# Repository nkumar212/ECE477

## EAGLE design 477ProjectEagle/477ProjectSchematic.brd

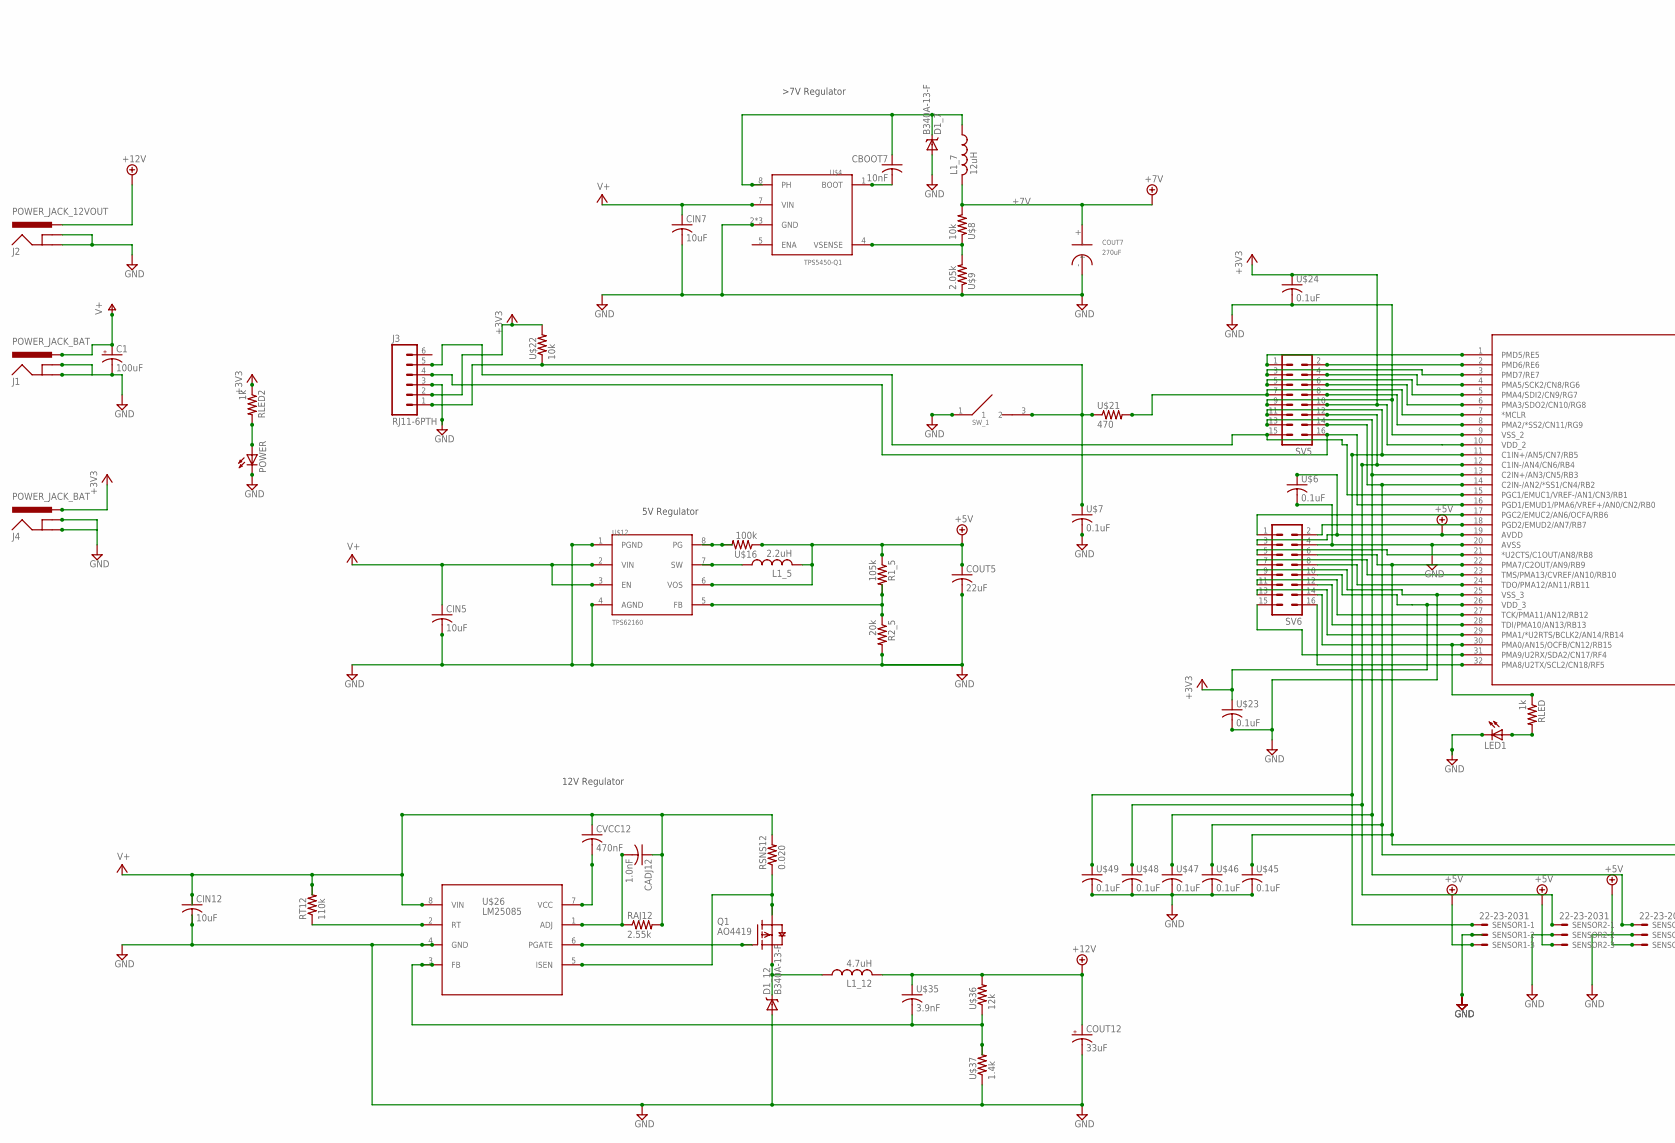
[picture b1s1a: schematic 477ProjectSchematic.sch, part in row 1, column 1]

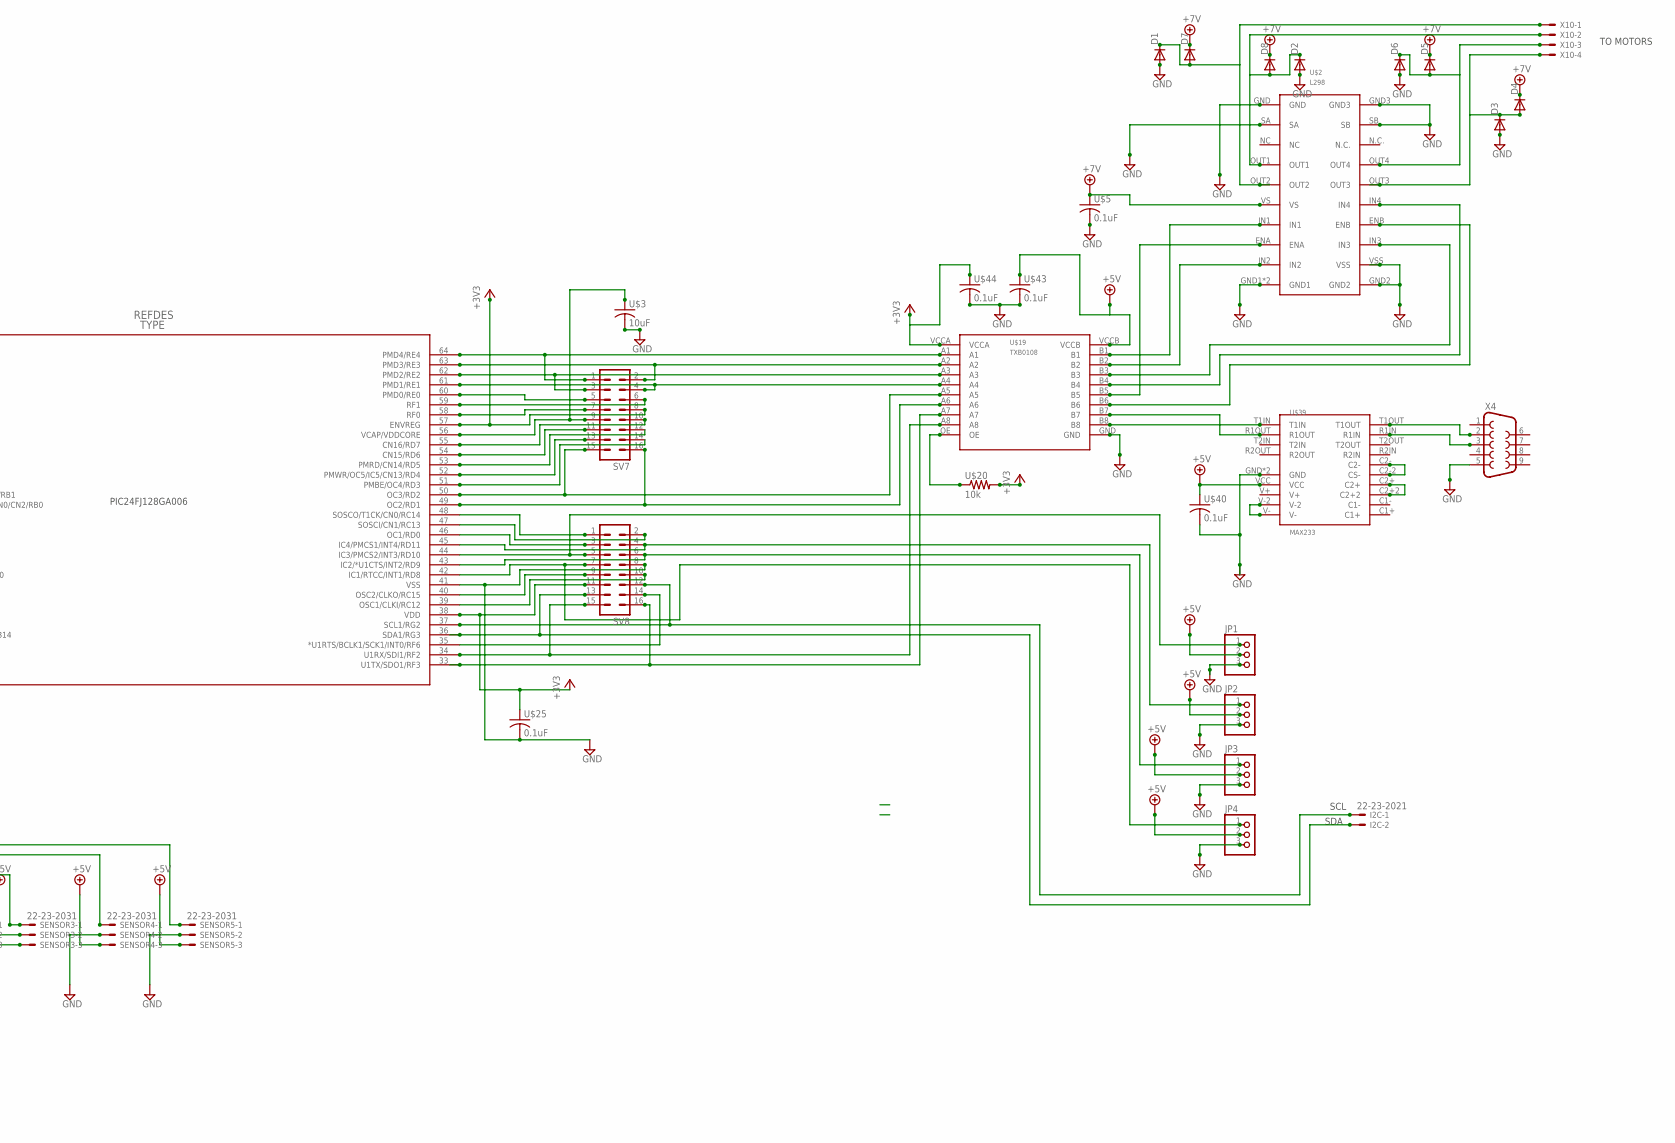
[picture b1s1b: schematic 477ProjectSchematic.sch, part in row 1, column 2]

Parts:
C1: 100uF; E3,5-8
CADJ12: 1.0nF; C1206
CBOOT7: 10nF; C1206
CIN5: 10uF; C1206
CIN7, CIN12: 10uF; C1210
COUT5: 22uF; C1206
COUT7: 270uF; CAPSMT_62_J80
COUT12: 33uF; D/7343-31W
CVCC12: 470nF; C1206
D1, D2, D3, D4, D5, D6, D7, D8: DIODE-DO-214AC; DO-214AC
D1_7, D1_12: B340A-13-F; SMA-DIODE
I2C: 22-23-2021
J1, J4: POWER_JACK_BAT; POWER_JACK_PTH
J2: POWER_JACK_12VOUT; POWER_JACK_PTH
J3: RJ11-6PTH; RJ11-6
JP1, JP2, JP3, JP4: PINHD-1X3; 1X03
L1_5: 2.2uH; SDR0403
L1_7: 12uH; SRR1210
L1_12: 4.7uH; SLF10165
LED1: LEDSMT1206; 1206
POWER: LEDSMT1206; 1206
Q1: AO4419; SOIC8
R1_5: 105k; R1206
R2_5: 20k; R1206
RAJ12: 2.55k; R1206
RLED, RLED2: 1k; R1206
RSNS12: 0.020; R1206
RT12: 110k; R1206
SENSOR1, SENSOR2, SENSOR3, SENSOR4, SENSOR5: 22-23-2031
SV5, SV6, SV7, SV8: MA08-2
SW_1: RESET_BUTTON; TACTILE-PTH-12MM
U$1: PIC24FJ128GA006-; TQFP64_10X10MC
U$2: L298
U$3: 10uF; C1206
U$4: TPS5450-Q1; PSOP-8
U$5, U$6, U$7, U$23, U$24, U$25, U$40, U$43, U$44, U$45, U$46, U$47, U$48, U$49: 0.1uF; C1206
U$8, U$20, U$22: 10k; R1206
U$9: 2.05k; R1206
U$12: TPS62160; MSOP-8
U$16: 100k; R1206
U$19: TXB0108
U$21: 470; R1206
U$26: LM25085; MSOP-8
U$35: 3.9nF; C1206
U$36: 12k; R1206
U$37: 1.4k; R1206
U$39: MAX233; SOIC-20
X4: DB9FEMALE; DB9
X10: 22-23-2041

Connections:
+3V3: J3.2, J4.PWR, RLED2.1, SV5.10, SV6.10, SV7.8, SV8.11, U$1.10 (VDD_2), U$1.26 (VDD_3), U$1.38 (VDD), U$1.57 (ENVREG), U$19.VCCA, U$20.2, U$22.2, U$23.1, U$24.1, U$25.1, U$44.1
+5V: COUT5.1, JP1.2, JP2.2, JP3.2, JP4.2, L1_5.B (2), R1_5.1, SENSOR1.3, SENSOR2.3, SENSOR3.3, SENSOR4.3, SENSOR5.3, SV6.3, U$1.19 (AVDD), U$6.1, U$12.6 (VOS), U$16.1, U$19.VCCB, U$39.VCC, U$40.1, U$43.1
+7V: COUT7.+, D4.C, D5.C, D7.C, D8.C, L1_7.B (2), U$2.VS, U$5.1, U$8.2
+12V: COUT12.+, J2.PWR, L1_12.2, U$35.1, U$36.2
GND: C1.-, CIN5.2, CIN7.2, CIN12.2, COUT5.2, COUT7.-, COUT12.-, D1.A, D1_7.-, D1_12.-, D2.A, D3.A, D6.A, J1.GND, J1.GNDBREAK, J2.GND, J2.GNDBREAK, J3.3, J4.GND, J4.GNDBREAK, JP1.3, JP2.3, JP3.3, JP4.3, LED1.C, POWER.C, R2_5.2, SENSOR1.2, SENSOR2.2, SENSOR3.2, SENSOR4.2, SENSOR5.2, SV5.9, SV6.4, SV6.9, SV8.8, SW_1.1, U$1.9 (VSS_2), U$1.20 (AVSS), U$1.25 (VSS_3), U$1.41 (VSS), U$2.GND, U$2.GND1, U$2.GND2, U$2.GND3, U$2.GNDPAD (GND1), U$2.SA, U$2.SB, U$2.VSS, U$3.2, U$4.2 (GND), U$4.6 (GND), U$4.PAD (GND), U$5.2, U$6.2, U$7.2, U$9.1, U$12.1 (PGND), U$12.4 (AGND), U$19.GND, U$23.2, U$24.2, U$25.2, U$26.4 (GND), U$37.1, U$39.GND, U$39.GND2 (GND), U$40.2, U$43.2, U$44.2, U$45.2, U$46.2, U$47.2, U$48.2, U$49.2, X4.5
unnamed: SENSOR1.1, SV5.11, U$1.11 (C1IN+/AN5/CN7/RB5), U$49.1
unnamed: SENSOR2.1, SV5.12, U$1.12 (C1IN-/AN4/CN6/RB4), U$48.1
unnamed: SENSOR3.1, SV5.13, U$1.13 (C2IN+/AN3/CN5/RB3), U$47.1
unnamed: SENSOR4.1, SV5.14, U$1.14 (C2IN-/AN2/*SS1/CN4/RB2), U$46.1
unnamed: SENSOR5.1, SV6.6, U$1.22 (PMA7/C2OUT/AN9/RB9), U$45.1
unnamed: SV5.1, U$1.1 (PMD5/RE5)
unnamed: J3.4, SV5.16, U$1.16 (PGD1/EMUD1/PMA6/VREF+/AN0/CN2/RB0)
unnamed: SV8.15, U$1.34 (U1RX/SDI1/RF2), U$19.A8
unnamed: SV8.16, U$1.33 (U1TX/SDO1/RF3), U$19.A7
unnamed: SV6.1, U$1.17 (PGC2/EMUC2/AN6/OCFA/RB6)
unnamed: SV5.2, U$1.2 (PMD6/RE6)
unnamed: JP3.1, SV8.6, U$1.43 (IC2/*U1CTS/INT2/RD9)
unnamed: U$39.V-, U$39.V-2
unnamed: J3.5, SV5.15, U$1.15 (PGC1/EMUC1/VREF-/AN1/CN3/RB1)
unnamed: SV7.1, U$1.64 (PMD4/RE4), U$19.A1
unnamed: CBOOT7.1, D1_7.+, L1_7.A (1), U$4.8 (PH)
unnamed: SV7.2, U$1.63 (PMD3/RE3), U$19.A2
unnamed: D2.C, D8.A, U$2.OUT1, X10.2
unnamed: D1.C, D7.A, U$2.OUT2, X10.1
unnamed: D5.A, D6.C, U$2.OUT4, X10.3
unnamed: D3.C, D4.A, U$2.OUT3, X10.4
unnamed: SV6.2, U$1.18 (PGD2/EMUD2/AN7/RB7)
unnamed: SV5.3, U$1.3 (PMD7/RE7)
unnamed: SV5.4, U$1.4 (PMA5/SCK2/CN8/RG6)
unnamed: CBOOT7.2, U$4.1 (BOOT)
unnamed: SV5.5, U$1.5 (PMA4/SDI2/CN9/RG7)
unnamed: SV5.6, U$1.6 (PMA3/SDO2/CN10/RG8)
unnamed: U$4.4 (VSENSE), U$8.1, U$9.2
unnamed: SV7.3, U$1.62 (PMD2/RE2), U$19.A3
unnamed: J3.1, SW_1.3 (2), U$7.1, U$21.1, U$22.1
unnamed: LED1.A, RLED.2
unnamed: SV7.4, U$1.61 (PMD1/RE1), U$19.A4
unnamed: D1_12.+, L1_12.1, Q1.1 (S), Q1.2 (S), Q1.3 (S)
unnamed: SV7.15, U$1.50 (OC3/RD2), U$19.A5
unnamed: U$26.3 (FB), U$35.2, U$36.1, U$37.2
unnamed: L1_5.A (1), U$12.7 (SW)
unnamed: U$12.8 (PG), U$16.2
unnamed: SV7.16, U$1.49 (OC2/RD1), U$19.A6
unnamed: U$2.IN1, U$19.B1
unnamed: R1_5.2, R2_5.1, U$12.5 (FB)
unnamed: U$2.IN4, U$19.B4
unnamed: U$2.IN2, U$19.B2
unnamed: U$2.IN3, U$19.B3
unnamed: U$2.ENA, U$19.B5
unnamed: U$2.ENB, U$19.B6
unnamed: SV6.5, U$1.21 (*U2CTS/C1OUT/AN8/RB8)
unnamed: U$19.B7, U$39.R1OUT
unnamed: RT12.1, U$26.2 (RT)
unnamed: U$19.B8, U$39.T1IN
unnamed: CVCC12.2, U$26.7 (VCC)
unnamed: CADJ12.2, RAJ12.1, U$26.1 (ADJ)
unnamed: U$39.T1OUT, X4.2
unnamed: Q1.5 (D), Q1.6 (D), Q1.7 (D), Q1.8 (D), RSNS12.1, U$26.5 (ISEN)
unnamed: Q1.4 (G), U$26.6 (PGATE)
unnamed: U$19.OE, U$20.1
unnamed: SV6.7, U$1.23 (TMS/PMA13/CVREF/AN10/RB10)
unnamed: SV8.1, U$1.48 (SOSCO/T1CK/CN0/RC14)
unnamed: SV6.8, U$1.24 (TDO/PMA12/AN11/RB11)
unnamed: U$39.C2-, U$39.C2-2 (CS-)
unnamed: SV6.11, U$1.27 (TCK/PMA11/AN12/RB12)
unnamed: SV6.12, U$1.28 (TDI/PMA10/AN13/RB13)
unnamed: SV6.13, U$1.29 (PMA1/*U2RTS/BCLK2/AN14/RB14)
unnamed: RLED.1, SV6.14, U$1.30 (PMA0/AN15/OCFB/CN12/RB15)
unnamed: SV7.9, U$1.56 (VCAP/VDDCORE), U$3.1
unnamed: SV8.2, U$1.47 (SOSCI/CN1/RC13)
unnamed: SV8.3, U$1.46 (OC1/RD0)
unnamed: JP2.1, SV8.4, U$1.45 (IC4/PMCS1/INT4/RD11)
unnamed: JP1.1, SV8.5, U$1.44 (IC3/PMCS2/INT3/RD10)
unnamed: U$39.C2+, U$39.C2+2
unnamed: JP4.1, SV8.7, U$1.42 (IC1/RTCC/INT1/RD8)
unnamed: SV8.9, U$1.40 (OSC2/CLKO/RC15)
unnamed: SV8.10, U$1.39 (OSC1/CLKI/RC12)
unnamed: SV7.11, U$1.54 (CN15/RD6)
unnamed: SV7.12, U$1.53 (PMRD/CN14/RD5)
unnamed: POWER.A, RLED2.2
unnamed: SV5.7, U$1.7 (*MCLR), U$21.2
unnamed: SV7.13, U$1.52 (PMWR/OC5/IC5/CN13/RD4)
unnamed: SV7.14, U$1.51 (PMBE/OC4/RD3)
unnamed: SV8.14, U$1.35 (*U1RTS/BCLK1/SCK1/INT0/RF6)
unnamed: U$39.R1IN, X4.3
unnamed: SV6.15, U$1.31 (PMA9/U2RX/SDA2/CN17/RF4)
unnamed: SV5.8, U$1.8 (PMA2/*SS2/CN11/RG9)
unnamed: SV6.16, U$1.32 (PMA8/U2TX/SCL2/CN18/RF5)
unnamed: SV7.10, U$1.55 (CN16/RD7)
unnamed: SV7.7, U$1.58 (RF0)
unnamed: SV7.6, U$1.59 (RF1)
unnamed: SV7.5, U$1.60 (PMD0/RE0)
SCL: I2C.1, SV8.12, U$1.37 (SCL1/RG2)
SDA: I2C.2, SV8.13, U$1.36 (SDA1/RG3)
V+: C1.+, CADJ12.1, CIN5.1, CIN7.1, CIN12.1, CVCC12.1, J1.PWR, RAJ12.2, RSNS12.2, RT12.2, U$4.7 (VIN), U$12.2 (VIN), U$12.3 (EN), U$26.8 (VIN)

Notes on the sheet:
5V Regulator
12V Regulator
TO MOTORS
PIC24FJ128GA006
SCL
SDA

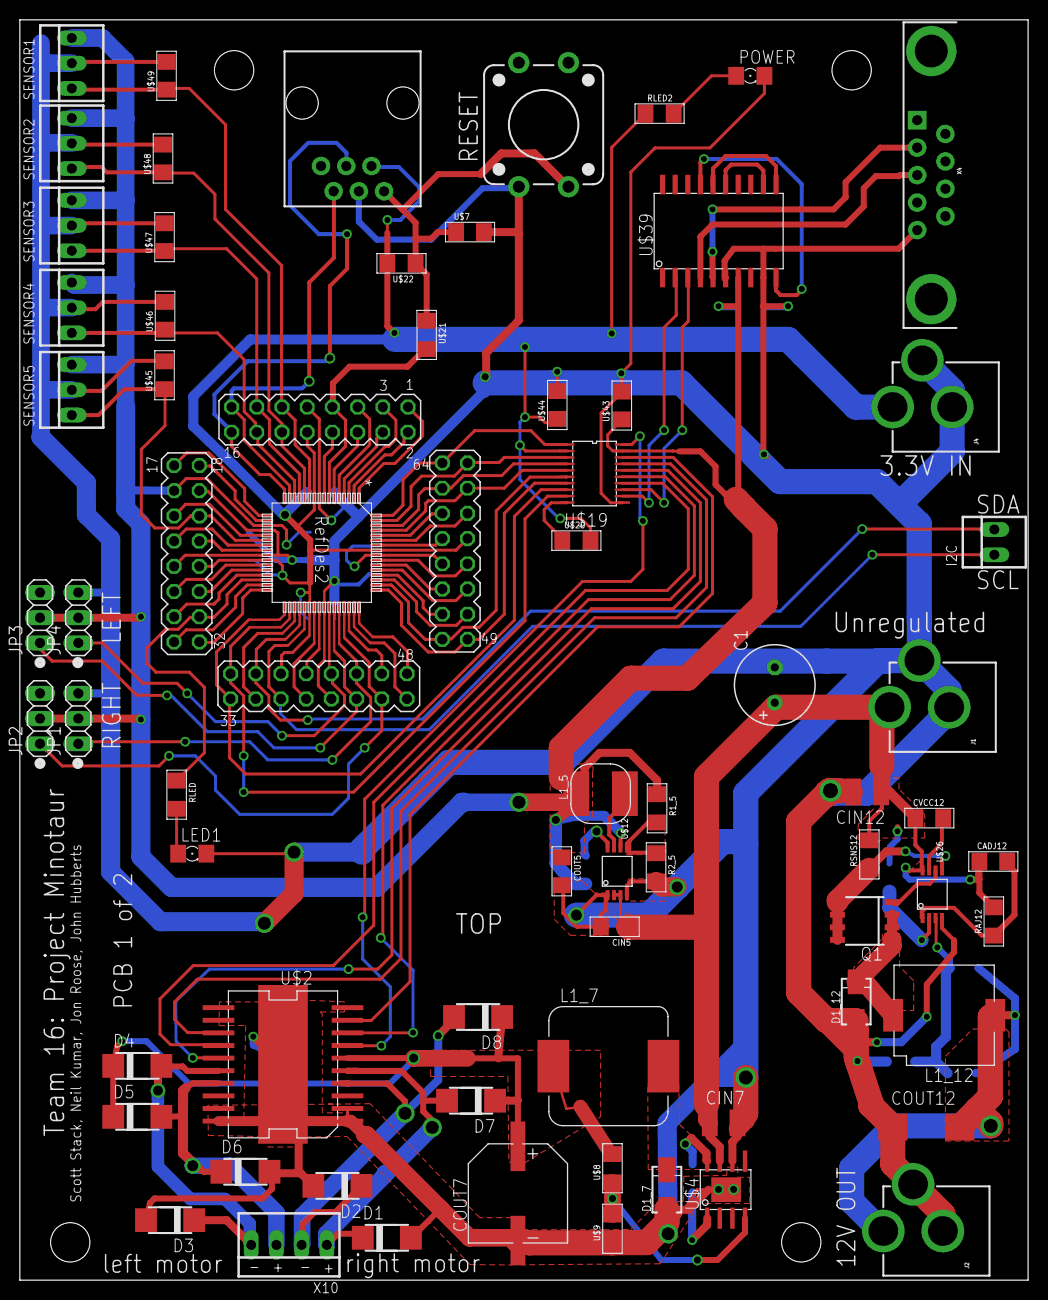
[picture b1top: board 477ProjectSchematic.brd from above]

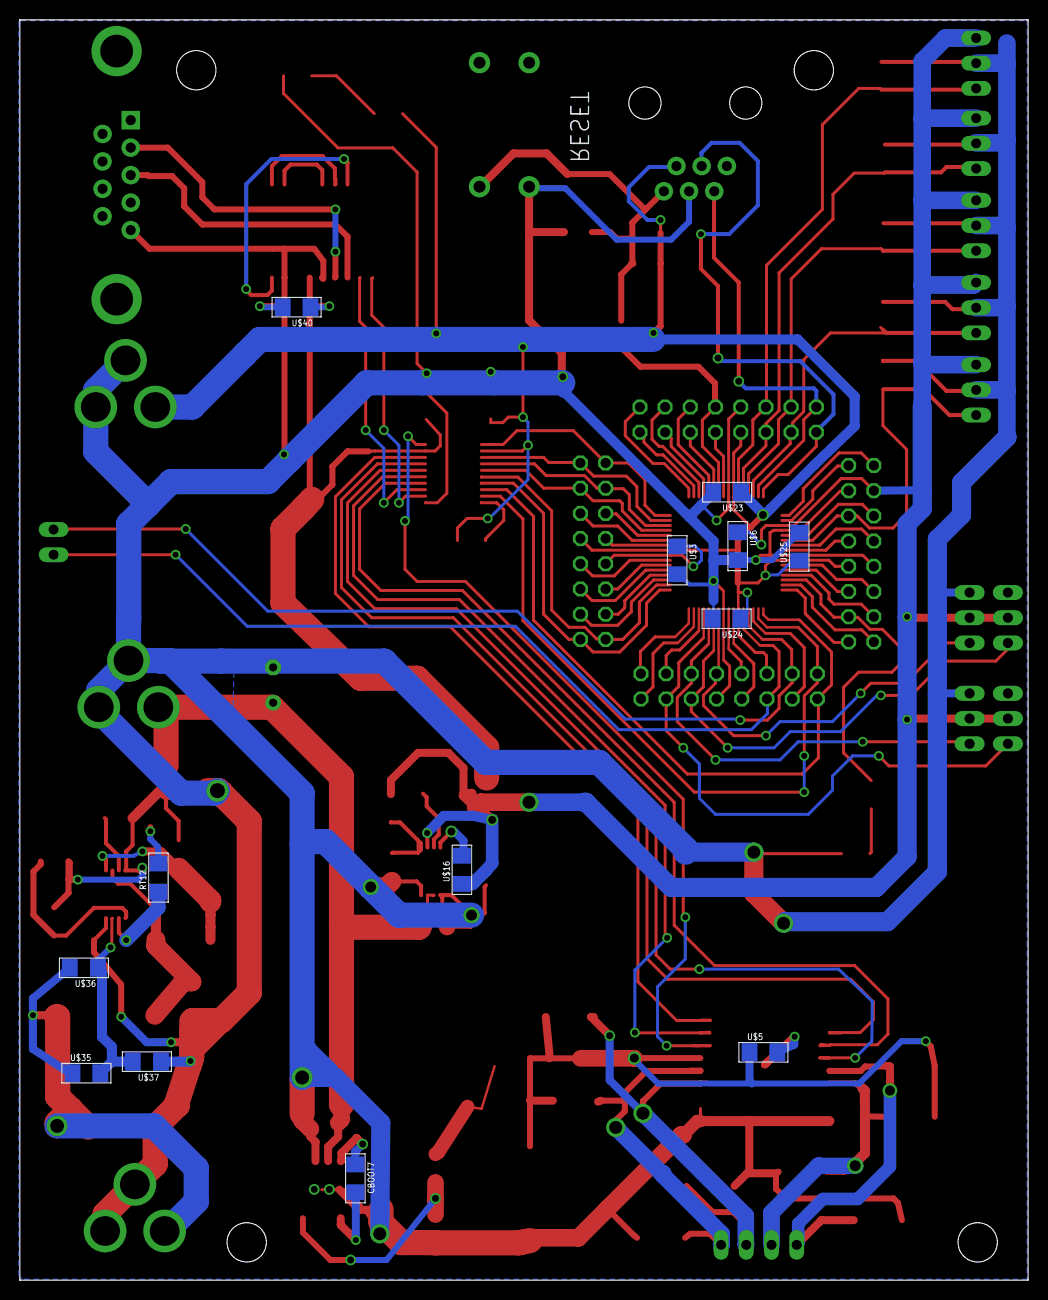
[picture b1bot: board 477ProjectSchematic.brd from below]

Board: 2 copper layers, 101.6 x 127.0 mm, 85 parts (13 on the bottom side), 95 nets.

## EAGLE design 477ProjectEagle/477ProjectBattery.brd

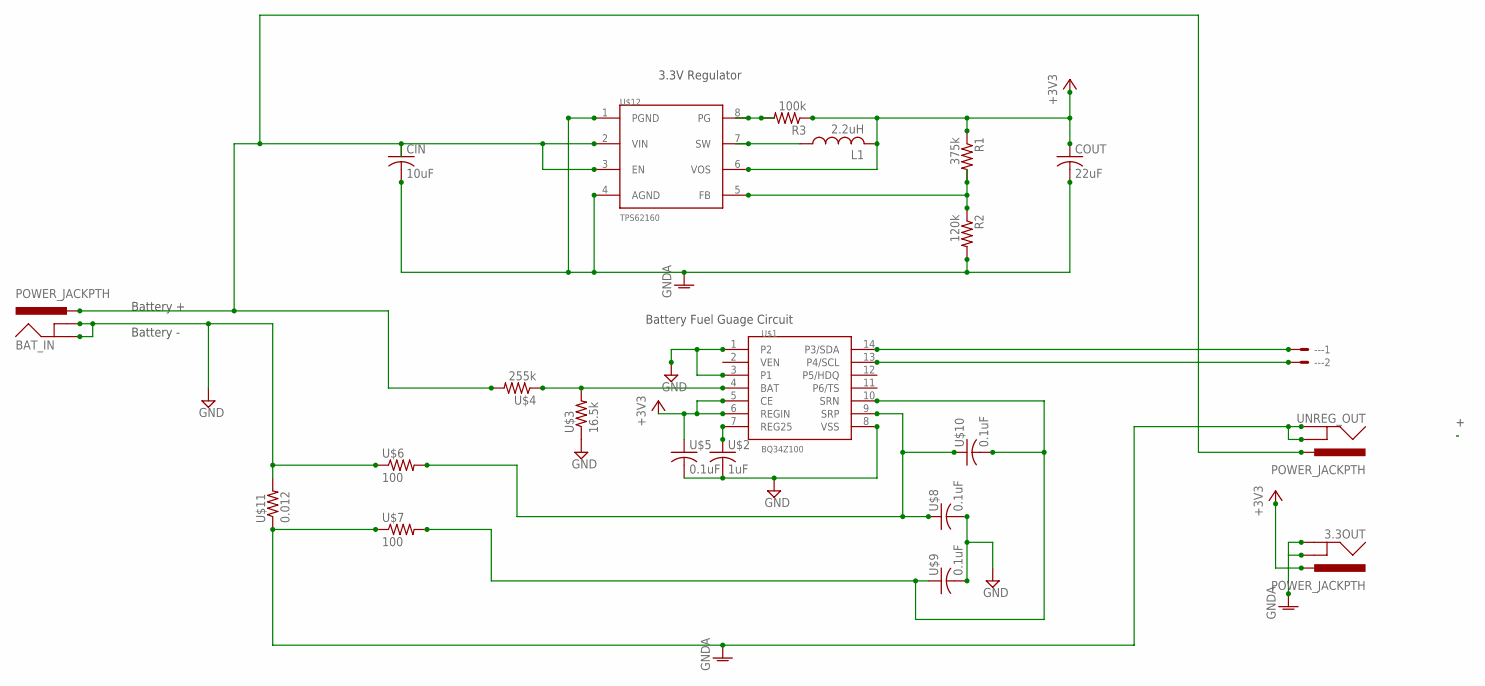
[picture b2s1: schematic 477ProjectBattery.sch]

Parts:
3.3OUT: POWER_JACKPTH; POWER_JACK_PTH
--: 22-23-2021
BAT_IN: POWER_JACKPTH; POWER_JACK_PTH
CIN: 10uF; C1206
COUT: 22uF; C1206
L1: 2.2uH; SDR0403
R1: 375k; R1206
R2: 120k; R1206
R3: 100k; R1206
U$1: BQ34Z100; SSOP-14
U$2: 1uF; C1206
U$3: 16.5k; R1206
U$4: 255k; R1206
U$5, U$8, U$9, U$10: 0.1uF; C1206
U$6, U$7: 100; R1206
U$11: 0.012; WSL2816
U$12: TPS62160; MSOP-8
UNREG_OUT: POWER_JACKPTH; POWER_JACK_PTH

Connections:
+3V3: 3.3OUT.PWR, COUT.1, L1.B (2), R1.1, R3.1, U$1.5 (CE), U$1.6 (REGIN), U$5.1, U$12.6 (VOS)
GND: BAT_IN.GND, BAT_IN.GNDBREAK, U$1.1 (P2), U$1.3 (P1), U$1.8 (VSS), U$2.2, U$3.1, U$5.2, U$6.1, U$8.2, U$9.2, U$11.2
GNDA: 3.3OUT.GND, 3.3OUT.GNDBREAK, CIN.2, COUT.2, R2.2, U$7.1, U$11.1, U$12.1 (PGND), U$12.4 (AGND), UNREG_OUT.GND, UNREG_OUT.GNDBREAK
unnamed: U$1.9 (SRP), U$6.2, U$8.1, U$10.1
unnamed: U$1.4 (BAT), U$3.2, U$4.1
unnamed: U$1.10 (SRN), U$7.2, U$9.1, U$10.2
unnamed: BAT_IN.PWR, CIN.1, U$4.2, U$12.2 (VIN), U$12.3 (EN), UNREG_OUT.PWR
unnamed: --.2, U$1.13 (P4/SCL)
unnamed: --.1, U$1.14 (P3/SDA)
unnamed: U$1.7 (REG25), U$2.1
unnamed: L1.A (1), U$12.7 (SW)
unnamed: R3.2, U$12.8 (PG)
unnamed: R1.2, R2.1, U$12.5 (FB)

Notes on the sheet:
3.3V Regulator
Battery +
Battery -
Battery Fuel Guage Circuit

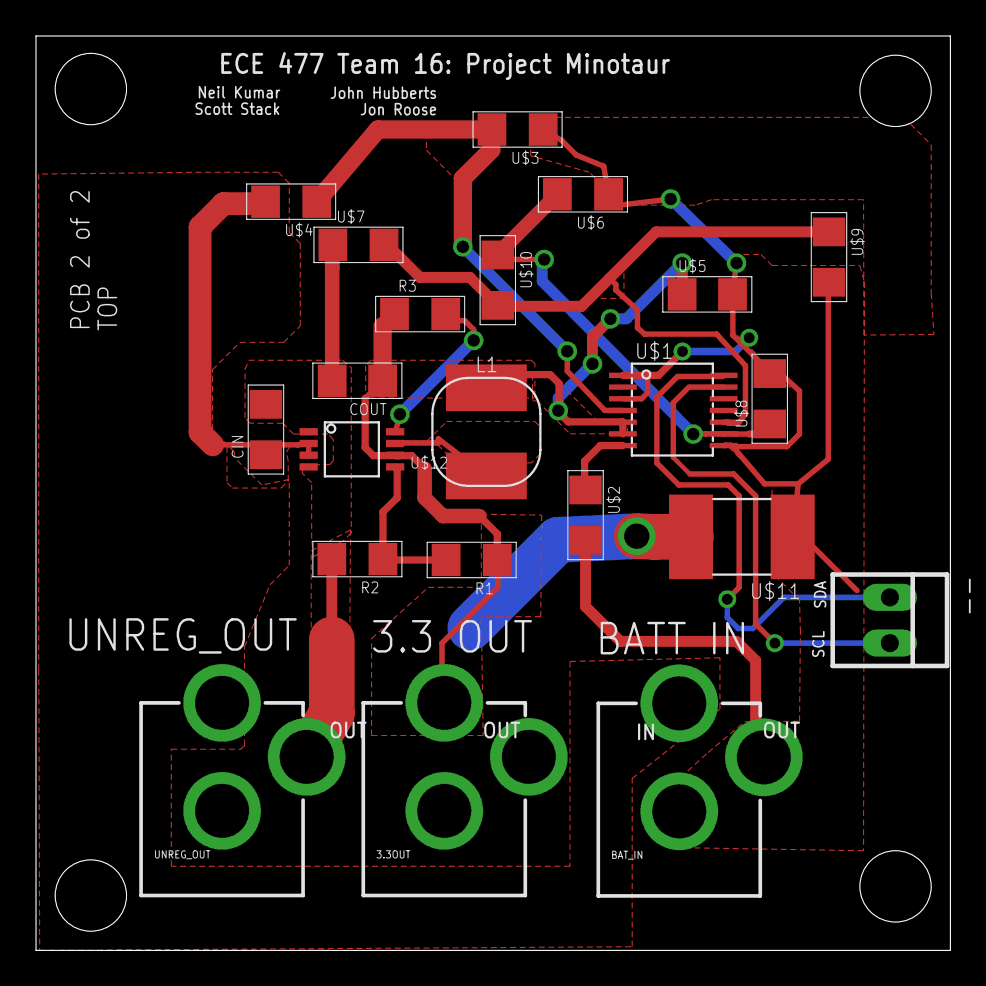
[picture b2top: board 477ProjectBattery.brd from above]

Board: 2 copper layers, 50.8 x 50.8 mm, 22 parts (0 on the bottom side), 13 nets.

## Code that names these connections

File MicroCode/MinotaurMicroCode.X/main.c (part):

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//Motor encoder code. Keeps trac of the number of ticks (can be a negative number)
//SEE ->>  http://en.wikipedia.org/wiki/Rotary_encoder  - Incremental rotary encoder section
void __attribute__((__interrupt__,__auto_psv__)) _T3Interrupt() {
    unsigned char ch1 = PORTDbits.RD10 << 4; //current value of ch1 pin
    unsigned char ch2 = PORTDbits.RD11; //current value of ch2 pin
    unsigned char currentstate = ch1 | ch2;


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    }


    ch1 = PORTDbits.RD8 << 4; //current value of ch1 pin
    ch2 = PORTDbits.RD9; //current value of ch2 pin.
    currentstate = ch1 | ch2;


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
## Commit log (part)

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2013-02-10 Started Schematic
    Created txb0108 and L298 parts
2013-02-10 Consolidated Parts
    I moved my parts from the NeilParts library to a new MinotaurParts
    library and added the schematic/layout for the PIC24FJ128GA006 to the
    Minotaur library
2013-02-10 deleted the test file.
2013-02-10 Added more parts to the eagle library
    Added BQ34Z100(battery fuel guage), TXS0104E (3.3-5 level converter),
    MAX233 (RS232 level conv)
2013-02-11 Created Project Minotaur library for PCB parts
2013-02-11 updated the eagle library
2013-02-11 Created Part
    Scott Created LM5005
2013-02-11 Updated the eagle library
    Deleted the eagle_files folder and moved the LM5005 part to the correct
    library.
2013-02-12 Created several new parts in eagle library
    Created the power regulator ICs
2013-02-12 Created micro code project!
    Created a project for the micro code! Copied all the ADC test functions
    to their own file and linked that file to the main file to make it a
    little neater.
2013-02-13 Created Parts
    I added the unmade parts for the 3/5V regulator as well as the 7V
    regulators
2013-02-13 Changed Schematic
    I moved a pin on the MIcro
2013-02-13 Created new eagle parts
    Created/Added parts for the power circuits. Mainly parts for the 12V
    circuit
2013-02-14 Updated Schematic
    I changed the Schematic and removed the Power and GND rails going all
    over the place. instead i used the "parts" from the supply1 and supply2
    libraries in eagle. these parts just rename a net list and are not
    associated with any package. i used the 3V3, 5V, 7V, 12V, and GND
    symbols from these libraries.
2013-02-14 Updated schematic
2013-02-14 Fixed Schematic
2013-02-15 Updated library with CS resistor
2013-02-15 Added the batttery circuit schematic!
2013-02-15 Made further edits to both schematics
    decoupling capacitors, values for passive components, RJ11 and SUBD
    connectors.
2013-02-16 Updated micro code and small schematic fix
    Added ADC code to micro project. The code initializes adc to capture
    data from all 5 sensors the interrupt when done.
    Also added decoupling caps to the ADC input lines.
2013-02-17 Battery PCB
    I created the battery PCB and started placing parts. gonna be tough to
    make it super small.
2013-02-18 Messed up the board.
    When i first created the board it was wrong, even though i got it to a
    1.5x1.5 in square. I am restarting the design based on the datasheet
    recommended layout.
2013-02-18 started main PCB layout - 12V supply done
    Started the PCB layout. Got the 12 volt power supply circuit done. We
    only have the Light version of eagle so I couldn't actually make the PCB
    the right size.
2013-02-18 More work on main PCB
    Fixed some trace sizes on 12V power supply. Fixed some library
    components to be the right size (Cout for the 7V power supply). Started
    laying out 7V power supply circuit
2013-02-18 Main PCB - started on 7V power supply
2013-02-18 Continued work on main PCB
    All components are in a rough position on the board. Everything just
    needs to be connected now...
2013-02-19 Made Major changes to the Battery PCB
    I finished up the Battery PCB and incorporated the recommended layout
    for the 3.3V source.
2013-02-19 Scott lab -- Work on main PCB
    Started connecting everything together. Made a bunch of progress.
2013-02-19 Worked on Battery PCB
    Finished up the Battery PCB
2013-02-20 minor changes to main PCB
2013-02-20 Battery PCB
    finished up board
2013-02-20 Fixed one power rail on main PCB
2013-02-21 Did a lot of work on the PCB design
    Added headers to pad out all micro pins. Routed pretty much everything
    to where it needs to go. Just need to fix hbridge and check accuracy of
    connections
2013-02-21 Uploading basic ffserver/ffmpeg code
2013-02-21 Adding depth sensing simulator
2013-02-21 Moving simulation into its own subdirectory
2013-02-21 Battery PCB
    Finished up battery pcb, got rid of acute angles and turned off
    thermals.
2013-02-21 Finished routing everything for main PCB
2013-02-21 Scott Lab - PCB All connected
    Added kickback diodes to the HBridge circuit. Added power LED and status
    LED. Changed all external connectors to parts from the sparkfun library
    (DB9, barrel, RJ11). Need to add more silkscreen - label all
    connectionsto outside
2013-02-21 Scott lab - Minor tweaks to main PCB
2013-02-22 Battery PCB
    Updated the Name and Value silkscreen on the Battery PCB so they dont
    overlap, was pretty difficult to do and couldnt get all but got most.
2013-02-22 Battery PCB
    Made the Silkscreen text size smaller, no conflicts now.
2013-02-22 Minor changes to battery PCB
    Changed board size. Fixed acute angle. Fixed a polygon or two
2013-02-22 minor changes to PCBs
2013-02-24 small changes to main PCB
2013-02-25 Changes to main PCB!!!
    Took out I2C level converter. Changed encoder to GPIO pins
2013-02-25 Fixed thermals and traces on RJ-11 connector
    Scott Lab
2013-02-25 Fixed Schematic to include cap for internal reg
2013-02-26 Wrote Initialization Routines For PWM
    Wrote some initialization for PWM module. Tested it with new snazzy
    Oscilloscopes and it works. Set the PWM period to 15ms. Created a new
    source file to put Timer/PWM functions in.
2013-02-27 Added a bunch to micro code
    Added UART initialization. Set Baud rate to 19200. Initialized a timer
    to use as a timeout for receiving commands from Atom board. Set up
    interrupts for all modules.
2013-02-28 Worked on micro code
2013-03-02 Worked on PIC software
    Implemented a circular send and receive buffer for the UART. Tested it
    and got it working. Fixed the H-Bridge package. Wrote a txt document
    with all the things that need to be fixed on the PCB.
2013-03-04 Fixed some main PCB things
    Put standoff holes in board. Fixed encoder headers so that there are 4
    banks of 3 holed headers. (2 three holed headers per encoder.)
2013-03-05 Did some verification of the schematic
    Fixed resistor values for power supplies. Fixed the max 233 chip
    connections and the DB9 connections. Verified everything on the main PCB
    schematic except reset button and programming header.
2013-03-05 PCB is almost finalized.
    Scott Lab- Added bulk cap. added GND plane. Added lots of information on
    the silkscreen. Barrel connectors for all power sources. Verified and
    fixed programming header(added cap). Added barrel connectors to battery
    PCB and made standoff drill holes.
2013-03-06 small changes to code and PCB
    Scott
2013-03-07 Finishing touches on PCB
2013-03-07 FINAL PCB DESIGN!
    Scott Lab - take 1
2013-03-07 FINAL PCB DESIGN WITH PICTURES
    put the pdfs of the results in the folder
2013-03-18 Wrote H-Bridge test code
2013-03-19 Worked on embedded code
    Fixed the int to string function and got it to print sensor values.
    Sensor value controlled the speed of the motors. WASD now controlls
    direction through serial.
2013-03-21 Scott - Started working on input capture code
    Wrote the initialization routines for all 4 input capture inputs for the
    motor encoders. Also setup the input cap interrupt routines in the main
    C file. Still need to test initializations and find a way to determine
    direction of rotation. Got PCBs in today and both motors now work with
    the H-Bridge
2013-03-22 Adding Web UI
2013-03-23 Completed asynchronous key presses
2013-03-24 Updating to local copy - jroose
2013-03-24 Cleaning up prototyping code
2013-03-25 Began implementing IDS
2013-03-25 Multithreading progress
2013-03-25 Threaded client server
2013-03-26 Working on IDS
2013-03-26 Synching file deletes. I'm a git newb.
2013-03-26 Multithreading works
2013-03-27 Changed cnc.py to use txws instead of a custom implementation.
2013-03-28 Updating ids
2013-03-28 Working timer driven command queue!
2013-03-28 Communicating with a test server! Keepalive is functional!
2013-03-28 Initializing Kinect library
2013-03-28 Created kinect library
2013-03-30 Transferring development to disk image
2013-04-01 Cleaned up micro code and integrated the I2C
2013-04-01 cleaned out the object files in micro code
2013-04-07 Fixed embedded code to work w/ micro
2013-04-08 Lots of progress. Implemented third thread which allows commands from CNC server to stream in.
2013-04-09 Scott - Minor changes to embedded code
2013-04-09 john - serial
2013-04-09 Adding missing source files. Dang you git.
2013-04-10 modifying i2c code to be interrupt driven, still have not added modified function names to header files or changed any of the main fucntion to integrate functions
2013-04-10 finished up the i2c functions and edited the header file, still need to do the ISR and the main fucntion
2013-04-10 Added ISR to main function
2013-04-11 Worked on a lot of micro code
    redid the motor encoder code. Implemented the protocol to send and
    receive serial commands to/from the atom board. It can now receive the
    Motor command, the Get sensor values command, and the get battery
    percentage command. Also write some bare bones obstacle avoidance code.
2013-04-11 Committing ffserver.conf settingsy
2013-04-12 finished up i2c main fucntion, should be ready to test, we still need to write an initialization program that initializes the fuel gauge to the necessary battery specs
2013-04-12 Scott - Embedded code
    Got protocol working and some obstacle avoidance. Can now drive motors
    or get sensor data from protocol
2013-04-12 Committing slope frame command and serial communication.
2013-04-12 Comitting cnc server
2013-04-15 Scott - got motor encoders working
    Also fixed the issue with the motors
2013-04-15 Updating makefiles
2013-04-15 Preparing to burn flash drive. Added Plane Detection command wallframe.
2013-04-15 Updating modifications
2013-04-18 Adding missing files
2013-04-18 Adding points for A* Tracking
2013-04-19 adding the kinect files!
2013-04-19 Updating
2013-04-19 Played with 3d coordinates
2013-04-19 Played with 3d processing and added capture command.
2013-04-19 Website and i2c
    Skeleton of website in client.html. Also made some minor modifications
    to i2c code
2013-04-19 minor changes to micro code
    changed some IR sensor obstacle avoidance stuff and added functionality
    for new commands
2013-04-20 Adding some files I missed
2013-04-20 Uploading new cnc.py with IP address listings for new connections
2013-04-20 Created camera control from web browser. Can now select 5 modes of video. Modes are: 3dX, 3dY, 3dZ, 3dXYZ "Rainbow", and "Walls" mode
2013-04-20 Implemented 5 types of video commands from browser
2013-04-20 Finished implementing several selectable camera views. They are built into the client.html interface and cnc.py F1 - 3dX F2 - 3dY F3 - 3dZ F4 - 3dXYZ - Rainbow F5 - WallView F6 - Live
2013-04-21 Attempting wall detection with DFT
2013-04-21 Adding missing commands
2013-04-22 Merged position tracking and previous updates made to minotaur while working. Worked on wall finding callibration.
2013-04-22 Small changes to the client webpage
2013-04-22 Updating cnc files with install.sh - a script to install cnc software
2013-04-22 Created metric data feedback
2013-04-22 Working on Minos communications. Extended Minotaur class and moved serial functionality to Minotaur from IDS class.
2013-04-22 Added metrics to web interface
2013-04-22 Implemented client side metric feedback.
2013-04-22 Motor encoders partially working. There appears to be a problem with Minos' serial connection.
2013-04-23 further updated the website
2013-04-23 minor fixes to website
2013-04-25 2D fourier transforms for identifying planes is complete! Requires additional camera callibration to improve accuracy. Need to implement gradient function to search for highpoints.
2013-04-25 fixed the website video and added a couple things
2013-04-26 Fourier transform wall detections like a boss!
2013-04-28 Implemented turn radius movement with motor encoders.
2013-04-28 Adding sanity check to motor encoders
2013-04-29 Updating turning function
2013-04-29 Goddamn circular buffers

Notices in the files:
parts and their libraries:
SparkFun-Connectors: Licensing: CC v3.0 Share-Alike You are welcome to use this library for commercial purposes.
